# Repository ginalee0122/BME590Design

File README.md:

# BME 590 Design
## LED Device Prototyping Project
###### Where Things Are
- Arduino code is in the 'Software' folder
- Schematic and PCB designs are in the 'Hardware' folder
###### Design Features and Flaws
- met all the constraints: runs on single battery up to 9 V, electronics connected to a single PCB, weighs less than 1 lb, all dimensions are less than 6 in, definitely costs less than $50, battery is easily replaceable
- is waterproof
- tightly encloses the board and the battery with minimum extra space inside the case, minimizing the device size
- securely holds the board and the battery in place; does not move around or fall apart even when shaken violently upside down
- easy to change battery
- the case is light-colored (almost semi-transparent) that you can see the changing LED responses with the lid closed
- the lid snugly fits in most of the times but not all the time; could be fixed by having a slightly more spacious lid

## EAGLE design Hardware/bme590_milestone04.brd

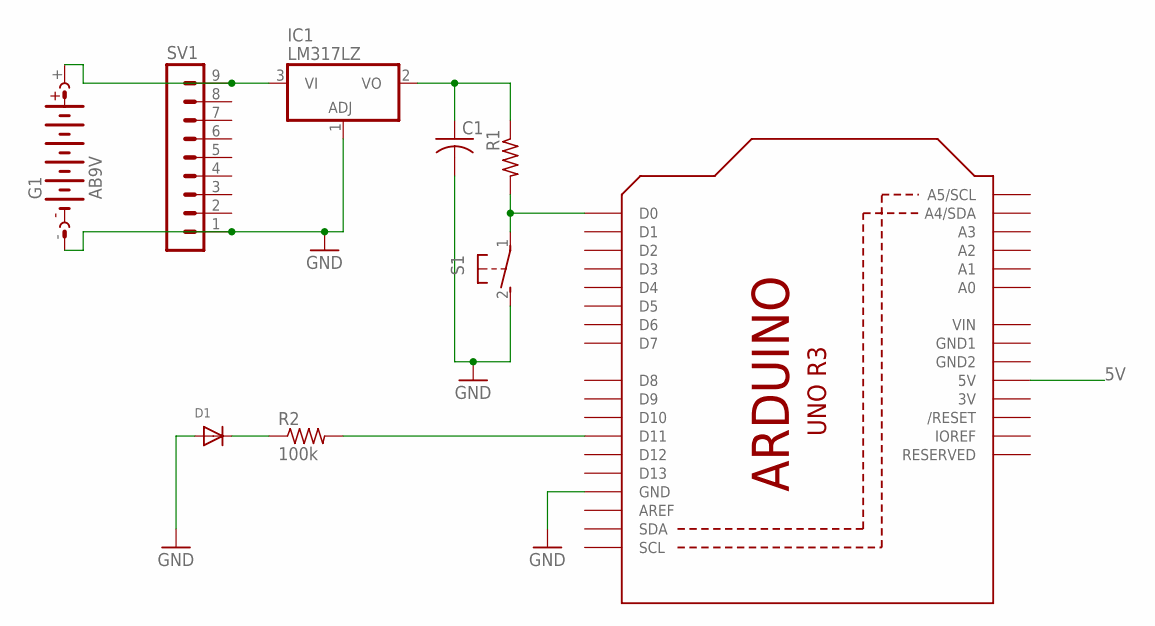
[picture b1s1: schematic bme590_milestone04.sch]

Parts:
C1: C-USC0805; C0805
D1: DIODEDO-1N4148; DO-1N4148
G1: AB9V
IC1: LM317LZ; TO92
R1: R-US_M0805; M0805
R2: 100k; R0805
S1: 31-XX; B3F-31XX
SV1: MA09-1W
U1: ARDUINOR3-DIMENSION; ARDUINOR3

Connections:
3V: U1.3V
5V: U1.5V
GND: C1.2, D1.A, G1.-, IC1.1 (ADJ), S1.2 (S), SV1.1, U1.GND
GND1: U1.GND1
GND2: U1.GND2
unnamed: G1.+, IC1.3 (VI), SV1.9
unnamed: R2.2, U1.D11
unnamed: C1.1, IC1.2 (VO), R1.1
unnamed: R1.2, S1.1, U1.D0
unnamed: D1.C, R2.1
VIN: U1.VIN

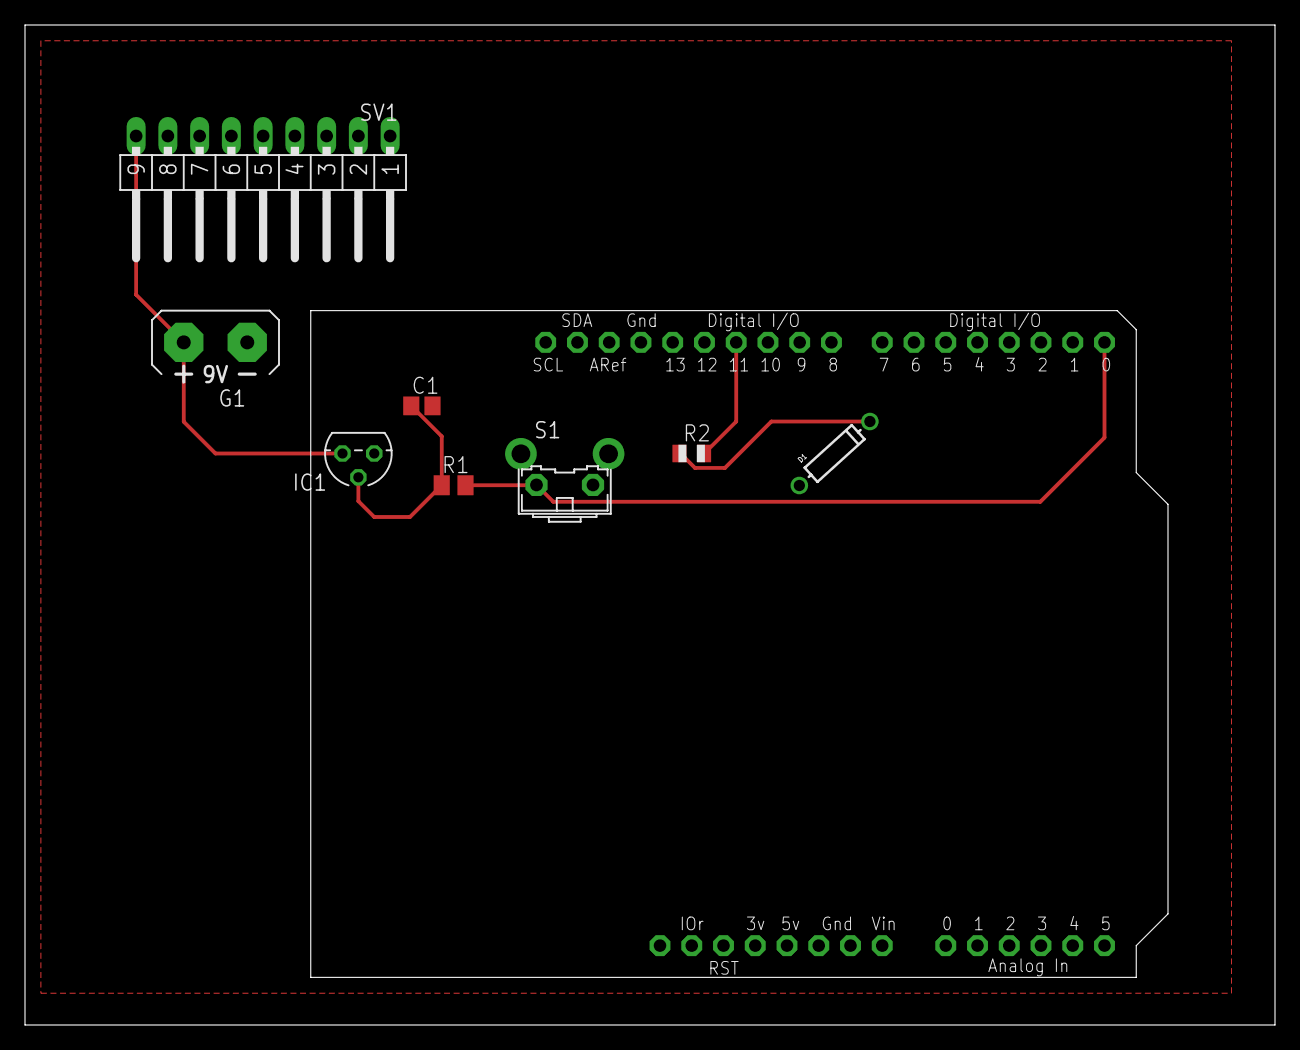
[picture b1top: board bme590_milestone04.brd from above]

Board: 2 copper layers, 100.0 x 80.0 mm, 9 parts (0 on the bottom side), 6 nets.

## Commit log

2018-11-01 milestone 03
2018-11-08 milestone 4 and some folder reorg
2018-11-15 updated PCB with polygon and other stuff
2018-12-13 light project is done YAY
